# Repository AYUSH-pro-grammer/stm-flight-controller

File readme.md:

## Flight Controller
A flight controller I designed to understand more about how drones are stable and how all the sensors interact. I created my own custom PCB using KiCad which includes an STM32F405, IMU, Magnetometer and Barometer. It has been a great way to learn about embedded systems, sensor calibration and PCB design, but has shown me what can go wrong when creating hardware. There is still plenty to learn before its ready to fly!

## How it works

This is a flight controller board which I have designed to learn how drones work and how they stay stable. The board contains an STM32F405 microcontroller as well as several sensors.

STM32F405 - This is the central processing unit of the board. It collects and processes the data from the sensors.
MPU6050 - The MPU6050 contains an accelerometer and gyroscope to give an understanding of the movement, rotation and tilting of the drone.
LIS3MDL - The LIS3MDL contains a magnetometer, which works like a digital compass.
BMP280 - The BMP280 gives information about the air pressure and temperature. The pressure can be used to determine the altitude of the drone.
Power management - There is a power management circuit on the board to provide the correct voltages to each of the components.
Communication - The sensors are connected to the STM32F405 using I2C. This means the microcontroller can collect the data from the sensors.

## Assembly

Put the components together following the KiCad PCB and BOM layout. Pay attention to the orientation of the components (particularly the ICs, diodes and connectors). Once assembled, make sure there are no solder bridges or incorrect solder joints before powering on.

## Programming

The STM32F405 can be programmed using the SWD connector. Simply connect the SWDIO, SWCLK and GND pins. Also connect the 3.3V reference pin. Using STM32CubeProgrammer the firmware can be flashed.

## Firmware

The firmware consists of using the Betaflight open source flight controller firmware ([https://github.com/betaflight/betaflight](https://github.com/betaflight/betaflight)). The board uses an STM32F405 with MPU6050, LIS3MDL and BMP280.

The firmware will need to be configured for the custom board. This includes pin configuration, sensor connection and so on. You can find the source code and build instructions in the Betaflight repository.

## Images

**Schematic View**

**PCB View**

**Front View**

**Back View**

# BOM 

| Reference | Component | Quantity | Link | Cost |
|---|---|---:|---|---:|
| C1; C5 | YAGEO 10pF 0402 | 2 | [LCSC](https://www.lcsc.com/product-detail/C3860506.html) | $0.0426 |
| C2 | CCTC 10uF 0805 | 1 | [LCSC](https://www.lcsc.com/product-detail/C380331.html) | $0.0420 |
| C3; C7; C13; C23; C24; C28; C29 | FH 100nF 0603 | 7 | [LCSC](https://www.lcsc.com/product-detail/C30926.html) | $0.0371 |
| C4; C6; C9; C11; C12; C17; C18; C19; C20; C21; C22 | FH 100nF 0603 | 11 | [LCSC](https://www.lcsc.com/product-detail/C30926.html) | $0.0583 |
| C8; C10 | Samsung 2.2uF 0603 | 2 | [LCSC](https://www.lcsc.com/product-detail/C23630.html) | $0.0240 |
| C14 | CCTC 10nF 0402 | 1 | [LCSC](https://www.lcsc.com/product-detail/C688874.html) | $0.0057 |
| C15; C16 | SAMWHA 1uF 0603 | 2 | [LCSC](https://www.lcsc.com/product-detail/C513775.html) | $0.0268 |
| C25; C26 | YAGEO 22uF 1210 | 2 | [LCSC](https://www.lcsc.com/product-detail/C5341638.html) | $1.0416 |
| C27 | KEMET 220pF 0603 | 1 | [LCSC](https://www.lcsc.com/product-detail/C3843887.html) | $0.1150 |
| C30 | Samsung Electro-Mechanics CL10A105KB8NNNC 1uF 50V 0603 | 1 | [LCSC](https://www.lcsc.com/product-detail/C15849.html) | $0.0159 |
| C31 | YAGEO 4.7uF 0805 25V | 1 | [LCSC](https://www.lcsc.com/product-detail/C5185457.html) | $0.0717 |
| C32 | FH 4.7uF 0805 25V | 1 | [LCSC](https://www.lcsc.com/product-detail/C274413.html) | $0.0617 |
| C33 | CCTC 10nF 0603 | 1 | [LCSC](https://www.lcsc.com/product-detail/C282516.html) | $0.0055 |
| C34 | FH 2.2nF 0603 | 1 | [LCSC](https://www.lcsc.com/product-detail/C1604.html) | $0.0109 |
| C35 | YAGEO 22pF 0603 | 1 | [LCSC](https://www.lcsc.com/product-detail/C2240294.html) | $0.0295 |
| C36 | YAGEO 10nF 0603 | 1 | [LCSC](https://www.lcsc.com/product-detail/C100042.html) | $0.0151 |
| C37; C38 | CCTC 47uF 1210 | 2 | [LCSC](https://www.lcsc.com/product-detail/C53327077.html) | $0.4938 |
| C39 | KEMET 100nF 0805 | 1 | [LCSC](https://www.lcsc.com/product-detail/C141162.html) | $0.0207 |
| D1 | DIODES SD103ATW-7-F Schottky diode array | 1 | [LCSC](https://www.lcsc.com/product-detail/C3758863.html) | $0.2775 |
| D2 | Hubei KENTO Blue LED 0603 | 1 | [LCSC](https://www.lcsc.com/product-detail/C2288.html) | $0.0104 |
| D3; D6 | Yongyu Red LED 0603 | 2 | [LCSC](https://www.lcsc.com/product-detail/C434419.html) | $0.0262 |
| D4 | Comchip SS54-HF | 1 | [LCSC](https://www.lcsc.com/product-detail/C3757794.html) | $1.0512 |
| D5 | High Diode BAT54C | 1 | [LCSC](https://www.lcsc.com/product-detail/C466637.html) | $0.0127 |
| FB1 | Murata BLM18PG121SN1D Ferrite Bead | 1 | [LCSC](https://www.lcsc.com/product-detail/C14709.html) | $0.0153 |
| FB2; FB3 | TAI-TECH HCB1608KF-121T30 120R Ferrite Bead 0603 | 2 | [LCSC](https://www.lcsc.com/product-detail/C353920.html) | $0.0174 |
| J1 | HMTCONN Micro-USB B SMD right-angle | 1 | [LCSC](https://www.lcsc.com/product-detail/C53121380.html) | $0.0704 |
| J2; J4; J23; J17; J18; J19; J20; J21; J22; J24; J25; J26; J28 | BOOMELE 2.54mm 1x40P male header strip (cut to length) | 2 | [LCSC](https://www.lcsc.com/product-detail/C2337.html) | $0.3150 |
| J3 | Hirose DM3AT-SF-PEJM5 MicroSD Connector | 1 | [LCSC](https://www.lcsc.com/product-detail/C114218.html) | $1.4048 |
| J29 | ronghe RH-5016 SMD Test Point (4.0x4.0mm pad) | 1 | [LCSC](https://www.lcsc.com/product-detail/C5199799.html) | $0.0926 |
| L1 | KOHERelec MDA7030-4R7M 4.7uH | 1 | [LCSC](https://www.lcsc.com/product-detail/C2847483.html) | $0.6353 |
| R1 | YAGEO 1k 0603 | 1 | [LCSC](https://www.lcsc.com/product-detail/C22548.html) | $0.0053 |
| R2 | SEI 332k 1206 | 1 | [LCSC](https://www.lcsc.com/product-detail/C2486051.html) | $0.0145 |
| R3; R4; R12; R19 | YAGEO 1.5k 0603 | 4 | [LCSC](https://www.lcsc.com/product-detail/C114668.html) | $0.0132 |
| R5 | Vishay 10k 0805 | 1 | [LCSC](https://www.lcsc.com/product-detail/C844937.html) | $0.0093 |
| R6; R7; R8; R9; R10; R11 | YAGEO 4.7k 0603 | 6 | [LCSC](https://www.lcsc.com/product-detail/C99782.html) | $0.0192 |
| R15 | SEI 35.7k 1206 | 1 | [LCSC](https://www.lcsc.com/product-detail/C2533888.html) | $0.1044 |
| R16 | YAGEO 0 ohm 0603 | 1 | [LCSC](https://www.lcsc.com/product-detail/C95177.html) | $0.0021 |
| R17 | TE Connectivity 10.5k 1206 | 1 | [LCSC](https://www.lcsc.com/product-detail/C2084092.html) | $0.2813 |
| R18 | YAGEO RT0603BRD073K2L 3.2k 0603 | 1 | [LCSC](https://www.lcsc.com/product-detail/C861375.html) | $0.0371 |
| SW1 | C&K PCM12 SPDT Slide Switch | 1 | [LCSC](https://www.lcsc.com/product-detail/C221841.html) | $1.2754 |
| SW2 | C&K PTS647 Tactile Switch | 1 | [LCSC](https://www.lcsc.com/product-detail/C2800043.html) | $0.2704 |
| U1 | TDK InvenSense MPU-6050 | 1 | [LCSC](https://www.lcsc.com/product-detail/C24112.html) | $20.2250 |
| U2 | ST STM32F405RGT6 | 1 | [LCSC](https://www.lcsc.com/product-detail/C15742.html) | $6.9460 |
| U3 | AMS1117-3.3 | 1 | [LCSC](https://www.lcsc.com/product-detail/C6186.html) | $0.2093 |
| U4 | ST LIS3MDLTR | 1 | [LCSC](https://www.lcsc.com/product-detail/C478483.html) | $3.7855 |
| U5 | Bosch BMP280 Digital Pressure Sensor | 1 | [Robu](https://robu.in/product/bosch-bmp280-digital-pressure-sensor/) | $8.3900 |
| U6 | TI TPS5431DDA | 1 | [LCSC](https://www.lcsc.com/product-detail/C1355446.html) | $3.7620 |
| U7 | ST USBLC6-2SC6 | 1 | [LCSC](https://www.lcsc.com/product-detail/C7519.html) | $0.1786 |
| Y1 | DIODES FY1600066 16MHz Crystal | 1 | [LCSC](https://www.lcsc.com/product-detail/C5717615.html) | $1.0077 |
| PCB | PCB fabrication | 1 | — | $8.00 |
| **TOTAL** | **Components + PCB fabrication** | | | **$60.5830** |

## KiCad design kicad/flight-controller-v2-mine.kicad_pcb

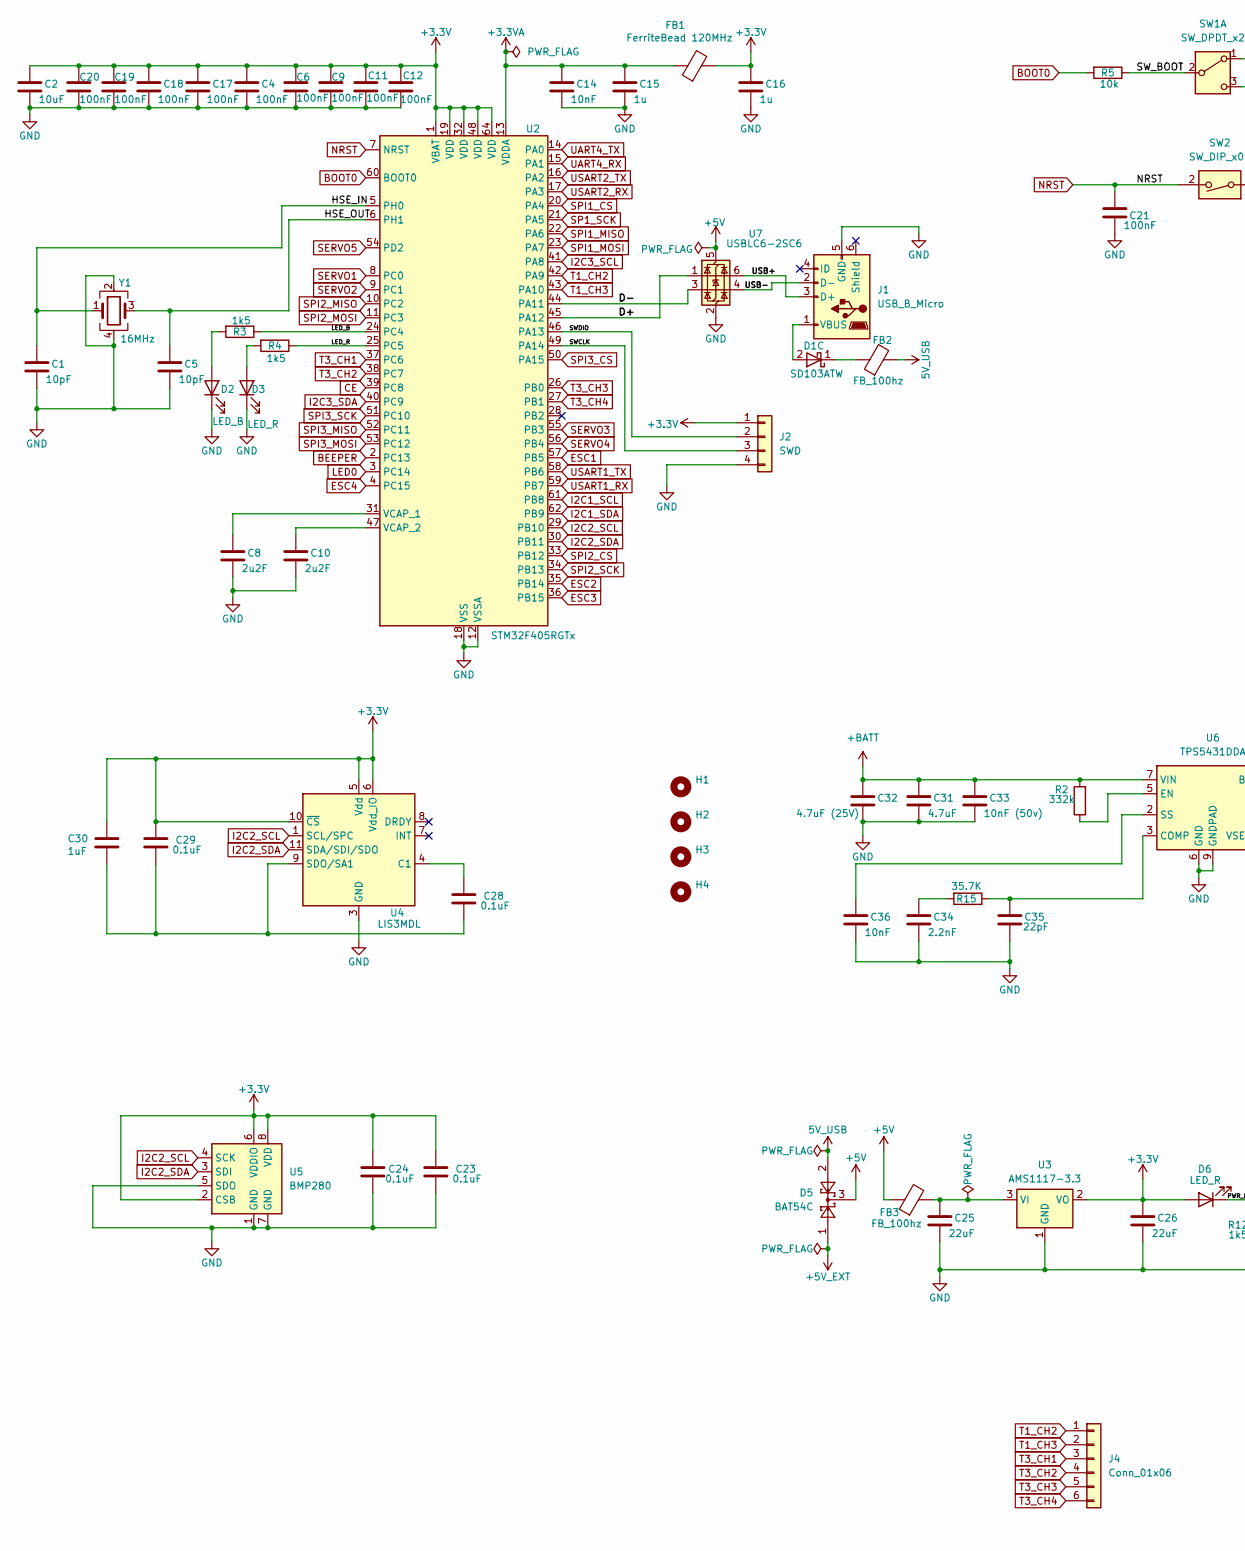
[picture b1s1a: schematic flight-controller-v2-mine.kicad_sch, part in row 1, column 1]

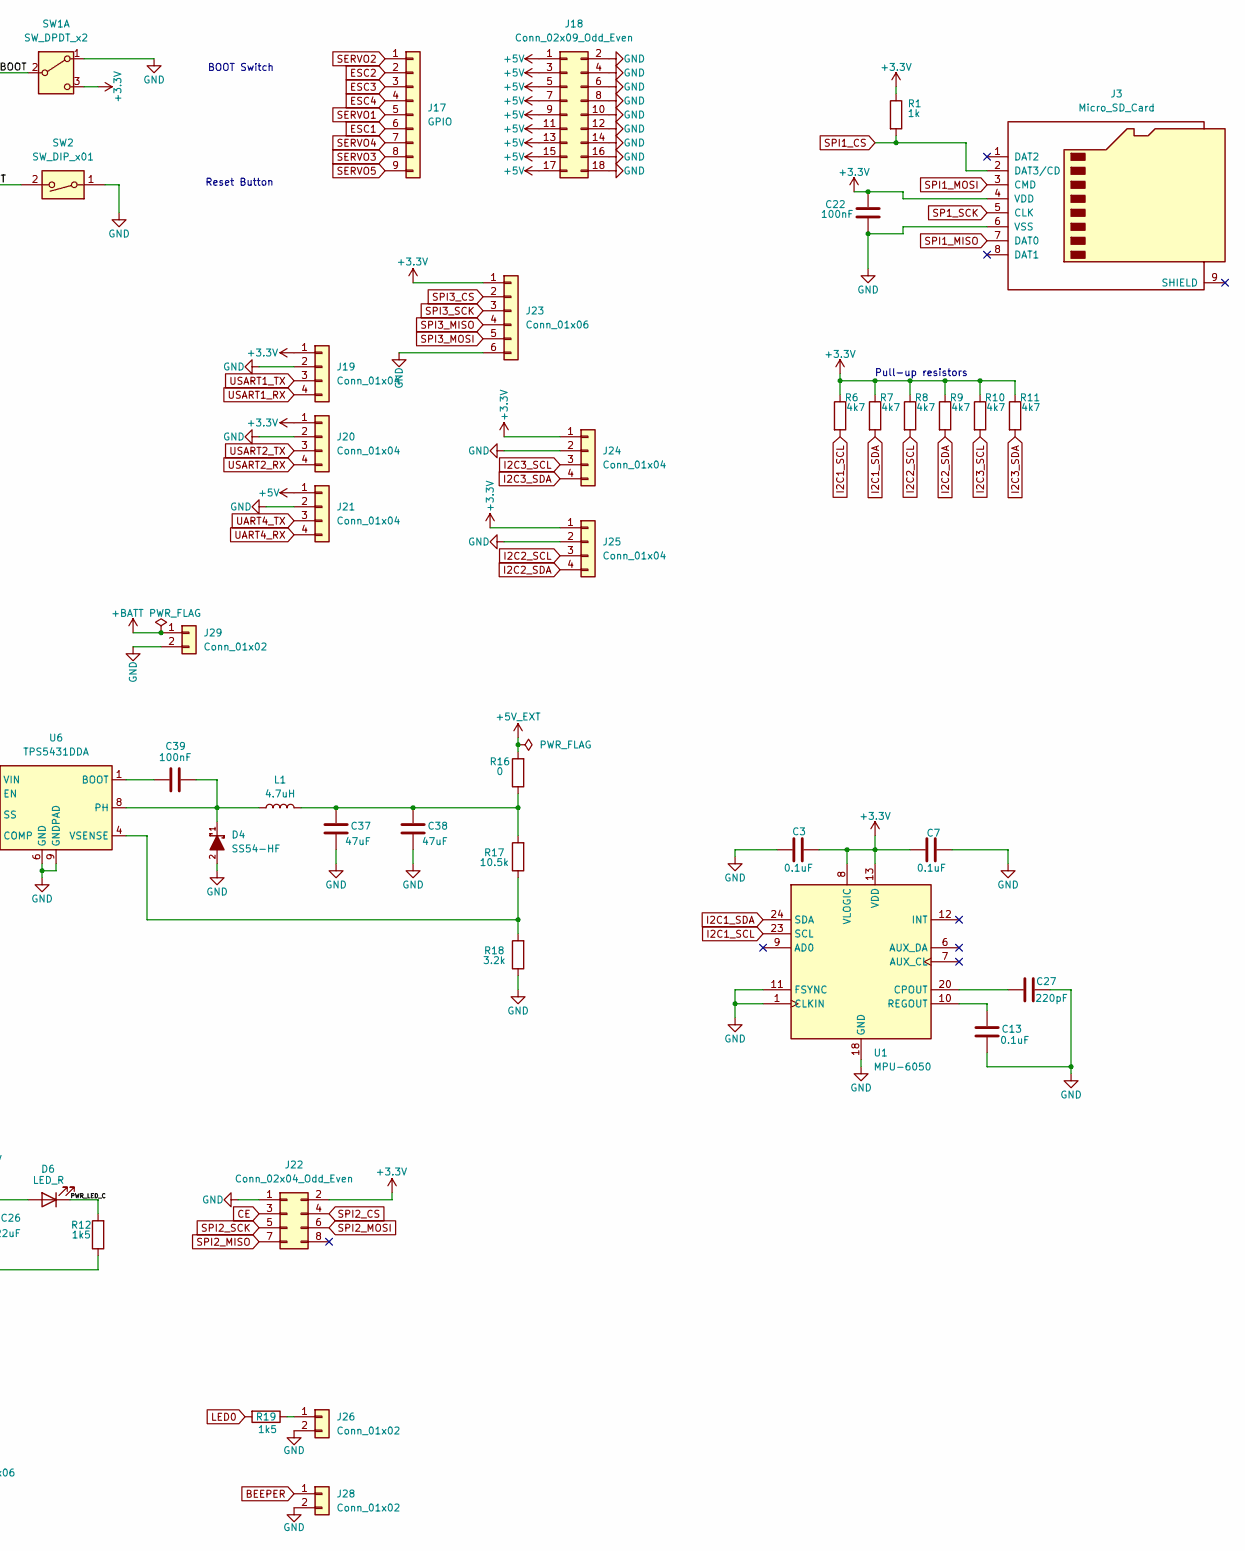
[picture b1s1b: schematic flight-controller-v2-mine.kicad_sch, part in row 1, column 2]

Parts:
C1, C5: 10pF; C_0402_1005Metric
C2: 10uF; C_0805_2012Metric
C3, C7, C13, C23, C24, C28, C29: 0.1uF; C_0603_1608Metric
C4, C6, C9, C11, C12, C17, C18, C19, C20, C21, C22: 100nF; C_0603_1608Metric
C8, C10: 2u2F; C_0603_1608Metric
C14: 10nF; C_0402_1005Metric
C15, C16: 1u; C_0603_1608Metric
C25, C26: 22uF; C_1210_3225Metric
C27: 220pF; C_0603_1608Metric
C30: 1uF; C_0603_1608Metric
C31: 4.7uF; C_0805_2012Metric
C32: 4.7uF (25V); C_0805_2012Metric
C33: 10nF (50v); C_0603_1608Metric
C34: 2.2nF; C_0603_1608Metric
C35: 22pF; C_0603_1608Metric
C36: 10nF; C_0603_1608Metric
C37, C38: 47uF; C_1210_3225Metric
C39: 100nF; C_0805_2012Metric
D1: SD103ATW; D_SOD-123
D2: LED_B; LED_0603_1608Metric
D3, D6: LED_R; LED_0603_1608Metric
D4: SS54-HF; D_SMA; MOUSER_PART_NUMBER 750-SS54-HF
D5: BAT54C; SOT-23
FB1: FerriteBead 120MHz; L_0603_1608Metric
FB2, FB3: FB_100hz; L_0603_1608Metric
H1, H2, H3, H4: MountingHole; MountingHole_4.3mm_M4_Pad_Via
J1: USB_B_Micro; USB_Mini-B_Lumberg_2486_01_Horizontal
J2: SWD; PinHeader_1x04_P2.54mm_Vertical
J3: Micro_SD_Card; microSD_HC_Hirose_DM3AT-SF-PEJM5
J4, J23: Conn_01x06; PinHeader_1x06_P2.54mm_Vertical
J17: GPIO; PinHeader_1x09_P2.54mm_Vertical
J18: Conn_02x09_Odd_Even; PinHeader_2x09_P2.54mm_Vertical
J19, J20, J21, J24, J25: Conn_01x04; PinHeader_1x04_P2.54mm_Vertical
J22: Conn_02x04_Odd_Even; PinHeader_2x04_P2.54mm_Vertical
J26, J28: Conn_01x02; PinHeader_1x02_P2.54mm_Vertical
J29: Conn_01x02; TestPoint_Pad_4.0x4.0mm
L1: 4.7uH; L_KOHERelec_MDA7030
R1: 1k; R_0603_1608Metric
R2: 332k; R_1206_3216Metric
R3, R4, R12, R19: 1k5; R_0603_1608Metric
R5: 10k; R_0805_2012Metric
R6, R7, R8, R9, R10, R11: 4k7; R_0603_1608Metric
R15: 35.7K; R_1206_3216Metric
R16: 0; R_0603_1608Metric
R17: 10.5k; R_1206_3216Metric
R18: 3.2k; R_0603_1608Metric
SW1: SW_DPDT_x2; SW_SPDT_PCM12
SW2: SW_DIP_x01; SW_SPST_PTS647_Sx38
U1: MPU-6050; InvenSense_QFN-24_4x4mm_P0.5mm
U2: STM32F405RGTx; LQFP-64_10x10mm_P0.5mm
U3: AMS1117-3.3; SOT-223-3_TabPin2
U4: LIS3MDL; LGA-12_2x2mm_P0.5mm
U5: BMP280; Bosch_LGA-8_2x2.5mm_P0.65mm_ClockwisePinNumbering
U6: TPS5431DDA; TI_SO-PowerPAD-8_ThermalVias
U7: USBLC6-2SC6; SOT-23-6
Y1: 16MHz; Crystal_SMD_5032-4Pin_5.0x3.2mm

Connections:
5V_USB: D5.2, FB2.2
+3.3V: C2.1, C3.2, C4.1, C6.1, C7.1, C9.1, C11.1, C12.1, C16.1, C17.1, C18.1, C19.1, C20.1, C22.1, C23.2, C24.2, C26.1, C29.2, C30.2, D6.2 (A), FB1.2, J2.1, J3.4 (VDD), J19.1, J20.1, J22.2, J23.1, J24.1, J25.1, R1.1, R6.1, R7.1, R8.1, R9.1, R10.1, R11.1, SW1.3 (C), U1.8 (VLOGIC), U1.13 (VDD), U2.1 (VBAT), U2.19 (VDD), U2.32 (VDD), U2.48 (VDD), U2.64 (VDD), U3.2 (VO), U4.5 (Vdd), U4.6 (Vdd_IO), U4.10 (~CS), U5.2 (CSB), U5.6 (VDDIO), U5.8 (VDD)
+3.3VA: C14.1, C15.1, FB1.1, U2.13 (VDDA)
+5V: D5.3, FB3.1, J18.1, J18.3, J18.5, J18.7, J18.9, J18.11, J18.13, J18.15, J18.17, J21.1, U7.5 (VBUS)
+5V_EXT: D5.1, R16.2
+BATT: C31.1, C32.1, C33.1, J29.1, R2.2, U6.7 (VIN)
/D+: U2.45 (PA12), U7.1 (I/O1)
/D-: U2.44 (PA11), U7.3 (I/O2)
/HSE_IN: C1.1, U2.5 (PH0), Y1.1
/HSE_OUT: C5.1, U2.6 (PH1), Y1.3
/LED_B: R3.1, U2.24 (PC4)
/LED_R: R4.1, U2.25 (PC5)
/SWCLK: J2.3, U2.49 (PA14)
/SWDIO: J2.2, U2.46 (PA13)
/SW_BOOT: R5.1, SW1.2 (B)
/USB+: J1.3 (D+), U7.6 (I/O1)
/USB-: J1.2 (D-), U7.4 (I/O2)
/power and connectors/PWR_LED_C: D6.1 (K), R12.2
BEEPER: J28.1, U2.2 (PC13)
BOOT0: R5.2, U2.60 (BOOT0)
CE: J22.3, U2.39 (PC8)
ESC1: J17.6, U2.57 (PB5)
ESC2: J17.2, U2.35 (PB14)
ESC3: J17.3, U2.36 (PB15)
ESC4: J17.4, U2.4 (PC15)
GND: C1.2, C2.2, C3.1, C4.2, C5.2, C6.2, C7.2, C8.2, C9.2, C10.2, C11.2, C12.2, C13.2, C14.2, C15.2, C16.2, C17.2, C18.2, C19.2, C20.2, C21.2, C22.2, C23.1, C24.1, C25.2, C26.2, C27.2, C31.2, C32.2, C33.2, C34.2, C35.2, C36.2, C37.2, C38.2, D2.1 (K), D3.1 (K), D4.2, J1.5 (GND), J2.4, J3.6 (VSS), J18.2, J18.4, J18.6, J18.8, J18.10, J18.12, J18.14, J18.16, J18.18, J19.2, J20.2, J21.2, J22.1, J23.6, J24.2, J25.2, J26.2, J28.2, J29.2, R12.1, R18.1, SW1.1 (A), SW2.1, U1.1 (CLKIN), U1.11 (FSYNC), U1.18 (GND), U2.12 (VSSA), U2.18 (VSS), U3.1 (GND), U4.3 (GND), U5.1 (GND), U5.5 (SDO), U5.7 (GND), U6.6 (GND), U6.9 (GNDPAD), U7.2 (GND), Y1.2, Y1.4
I2C1_SCL: R6.2, U1.23 (SCL), U2.61 (PB8)
I2C1_SDA: R7.2, U1.24 (SDA), U2.62 (PB9)
I2C2_SCL: J25.3, R8.2, U2.29 (PB10), U4.1 (SCL/SPC), U5.4 (SCK)
I2C2_SDA: J25.4, R9.2, U2.30 (PB11), U4.11 (SDA/SDI/SDO), U5.3 (SDI)
I2C3_SCL: J24.3, R10.2, U2.41 (PA8)
I2C3_SDA: J24.4, R11.2, U2.40 (PC9)
LED0: R19.2, U2.3 (PC14)
NRST: C21.1, SW2.2, U2.7 (NRST)
unnamed: C34.1, R15.2
unnamed: C37.1, C38.1, L1.2, R16.1, R17.2
unnamed: D1.2 (A), J1.1 (VBUS)
unnamed: D1.1 (K), FB2.1
unnamed: D2.2 (A), R3.2
unnamed: D3.2 (A), R4.2
unnamed: J26.1, R19.1
unnamed: C27.1, U1.20 (CPOUT)
unnamed: C13.1, U1.10 (REGOUT)
unnamed: C8.1, U2.31 (VCAP_1)
unnamed: C10.1, U2.47 (VCAP_2)
unnamed: C25.1, FB3.2, U3.3 (VI)
unnamed: C28.2, U4.4 (C1)
unnamed: C28.1, C29.1, C30.1, U4.9 (SDO/SA1)
unnamed: C39.1, U6.1 (BOOT)
unnamed: C35.1, R15.1, U6.3 (COMP)
unnamed: R2.1, U6.5 (EN)
unnamed: C39.2, D4.1, L1.1, U6.8 (PH)
unnamed: C36.1, U6.2 (SS)
unnamed: R17.1, R18.2, U6.4 (VSENSE)
SERVO1: J17.5, U2.8 (PC0)
SERVO2: J17.1, U2.9 (PC1)
SERVO3: J17.8, U2.55 (PB3)
SERVO4: J17.7, U2.56 (PB4)
SERVO5: J17.9, U2.54 (PD2)
SP1_SCK: J3.5 (CLK), U2.21 (PA5)
SPI1_CS: J3.2 (DAT3/CD), R1.2, U2.20 (PA4)
SPI1_MISO: J3.7 (DAT0), U2.22 (PA6)
SPI1_MOSI: J3.3 (CMD), U2.23 (PA7)
SPI2_CS: J22.4, U2.33 (PB12)
SPI2_MISO: J22.7, U2.10 (PC2)
SPI2_MOSI: J22.6, U2.11 (PC3)
SPI2_SCK: J22.5, U2.34 (PB13)
SPI3_CS: J23.2, U2.50 (PA15)
SPI3_MISO: J23.4, U2.52 (PC11)
SPI3_MOSI: J23.5, U2.53 (PC12)
SPI3_SCK: J23.3, U2.51 (PC10)
T1_CH2: J4.1, U2.42 (PA9)
T1_CH3: J4.2, U2.43 (PA10)
T3_CH1: J4.3, U2.37 (PC6)
T3_CH2: J4.4, U2.38 (PC7)
T3_CH3: J4.5, U2.26 (PB0)
T3_CH4: J4.6, U2.27 (PB1)
UART4_RX: J21.4, U2.15 (PA1)
UART4_TX: J21.3, U2.14 (PA0)
USART1_RX: J19.4, U2.59 (PB7)
USART1_TX: J19.3, U2.58 (PB6)
USART2_RX: J20.4, U2.17 (PA3)
USART2_TX: J20.3, U2.16 (PA2)

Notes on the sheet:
Reset Button
Pull-up resistors
BOOT Switch

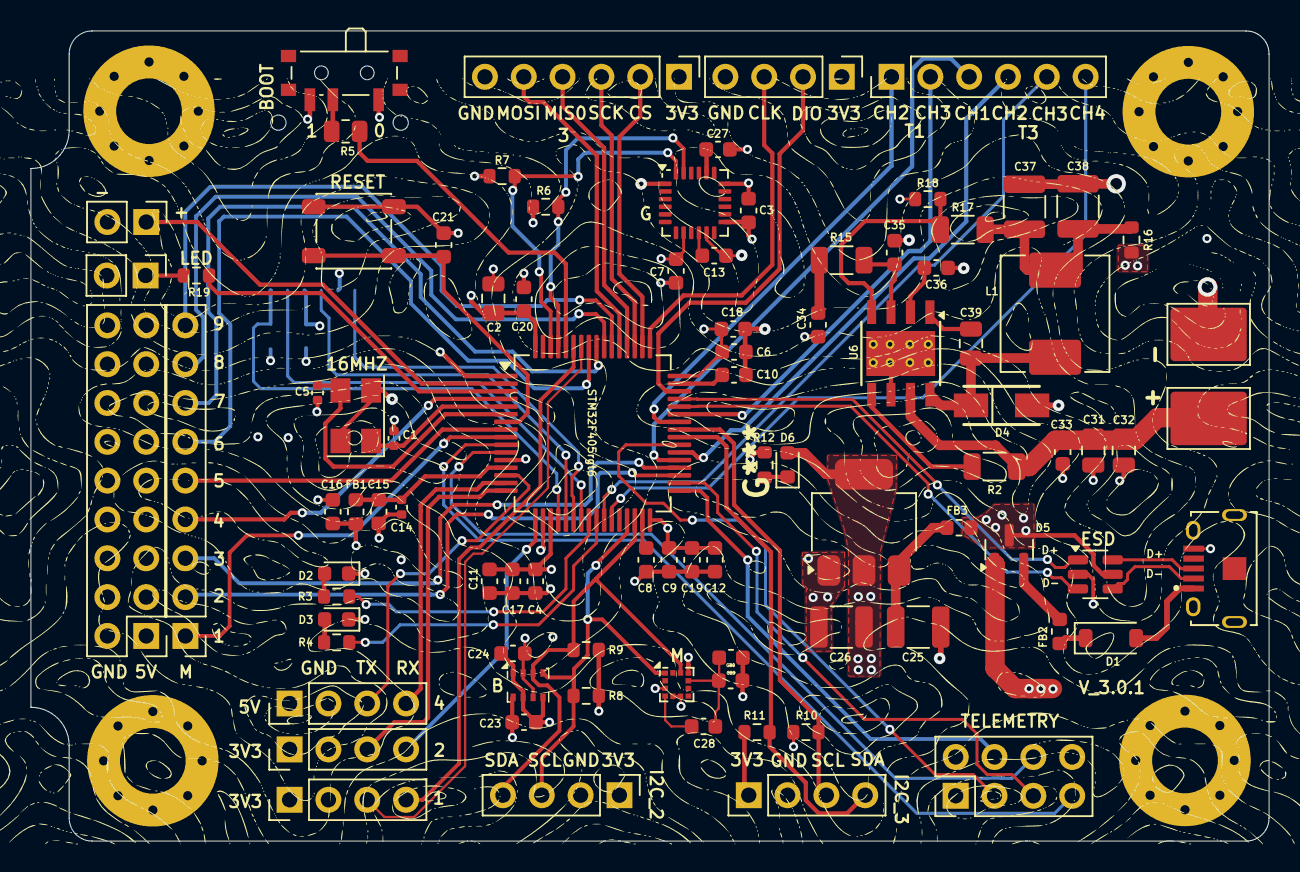
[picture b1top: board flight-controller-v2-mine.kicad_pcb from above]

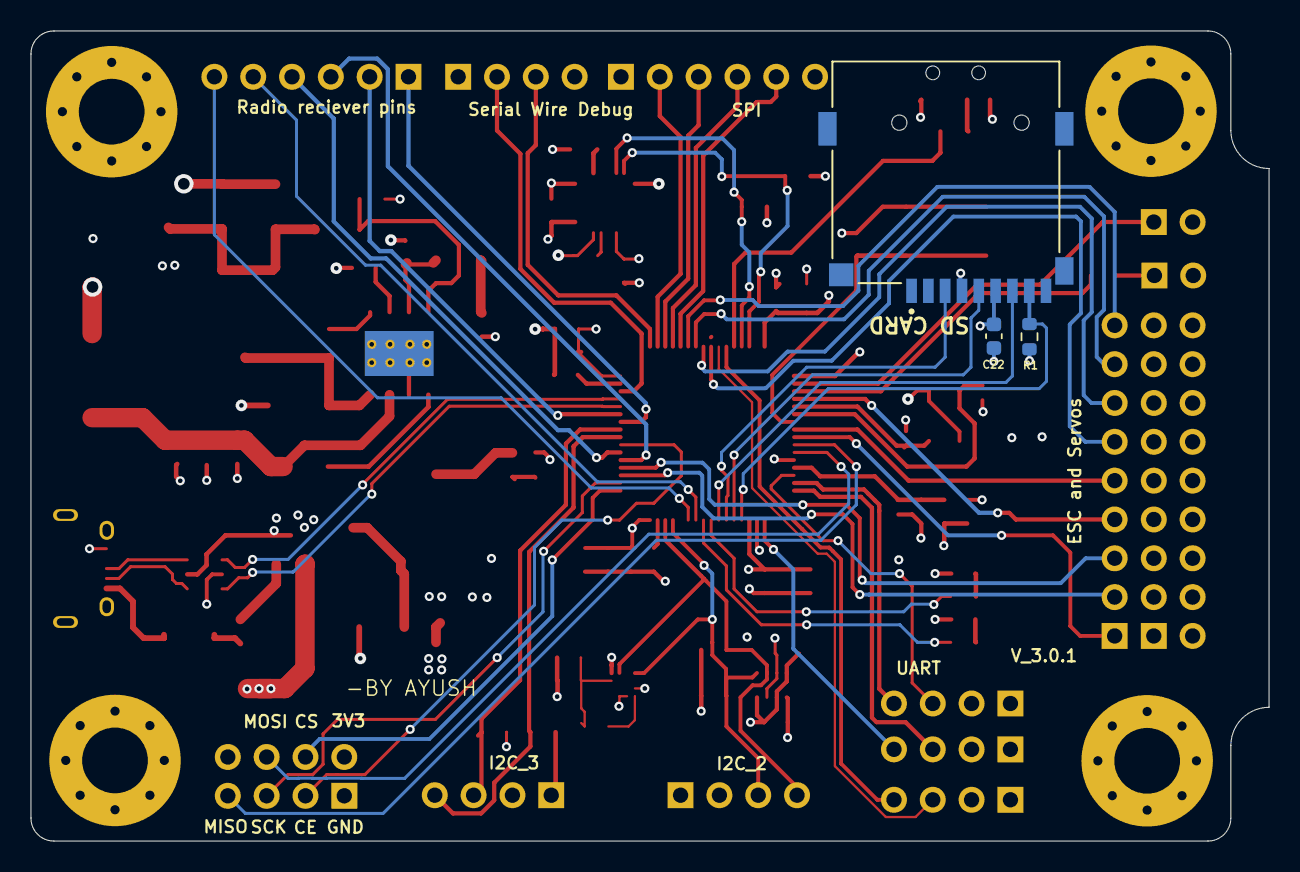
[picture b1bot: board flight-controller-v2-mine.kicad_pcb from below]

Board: 4 copper layers, 81.0 x 53.0 mm, 96 parts (3 on the bottom side), 83 nets.

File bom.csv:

Reference,Component,Quantity,Unit Price (USD),Product Link
"C1; C5","YAGEO 10pF 0402",2,0.0213,https://www.lcsc.com/product-detail/C3860506.html
"C2","CCTC 10uF 0805",1,0.0420,https://www.lcsc.com/product-detail/C380331.html
"C3; C7; C13; C23; C24; C28; C29","FH 100nF 0603",7,0.0053,https://www.lcsc.com/product-detail/C30926.html
"C4; C6; C9; C11; C12; C17; C18; C19; C20; C21; C22","FH 100nF 0603",11,0.0053,https://www.lcsc.com/product-detail/C30926.html
"C8; C10","Samsung 2.2uF 0603",2,0.0120,https://www.lcsc.com/product-detail/C23630.html
"C14","CCTC 10nF 0402",1,0.0057,https://www.lcsc.com/product-detail/C688874.html
"C15; C16","SAMWHA 1uF 0603",2,0.0134,https://www.lcsc.com/product-detail/C513775.html
"C25; C26","YAGEO 22uF 1210",2,0.5208,https://www.lcsc.com/product-detail/C5341638.html
"C27","KEMET 220pF 0603",1,0.1150,https://www.lcsc.com/product-detail/C3843887.html
"C30","Samsung Electro-Mechanics CL10A105KB8NNNC 1uF 50V 0603",1,N/A,https://www.lcsc.com/product-detail/C15849.html
"C31","YAGEO 4.7uF 0805 25V",1,0.0717,https://www.lcsc.com/product-detail/C5185457.html
"C32","FH 4.7uF 0805 25V",1,0.0617,https://www.lcsc.com/product-detail/C274413.html
"C33","CCTC 10nF 0603",1,0.0055,https://www.lcsc.com/product-detail/C282516.html
"C34","FH 2.2nF 0603",1,0.0109,https://www.lcsc.com/product-detail/C1604.html
"C35","YAGEO 22pF 0603",1,0.0295,https://www.lcsc.com/product-detail/C2240294.html
"C36","YAGEO 10nF 0603",1,0.0151,https://www.lcsc.com/product-detail/C100042.html
"C37; C38","CCTC 47uF 1210",2,0.2469,https://www.lcsc.com/product-detail/C53327077.html
"C39","KEMET 100nF 0805",1,0.0207,https://www.lcsc.com/product-detail/C141162.html
"D1","DIODES SD103ATW-7-F Schottky diode array - footprint check required",1,0.2775,https://www.lcsc.com/product-detail/C3758863.html
"D2","Hubei KENTO Blue LED 0603",1,0.0104,https://www.lcsc.com/product-detail/C2288.html
"D3; D6","Yongyu Red LED 0603",2,0.0131,https://www.lcsc.com/product-detail/C434419.html
"D4","Comchip SS54-HF",1,1.0512,https://www.lcsc.com/product-detail/C3757794.html
"D5","High Diode BAT54C",1,0.0127,https://www.lcsc.com/product-detail/C466637.html
"FB1","Murata BLM18PG121SN1D Ferrite Bead",1,0.0153,https://www.lcsc.com/product-detail/C14709.html
"FB2; FB3","TAI-TECH HCB1608KF-121T30 120R Ferrite Bead 0603",2,0.0087,https://www.lcsc.com/product-detail/C353920.html
"J1","HMTCONN Micro-USB B SMD right-angle - footprint check required",1,0.0704,https://www.lcsc.com/product-detail/C53121380.html
"J2; J4; J23; J17; J19; J20; J21; J24; J25; J26; J28","BOOMELE 2.54mm 1x40P male header strip - cut to length",2,0.1575,https://www.lcsc.com/product-detail/C2337.html
"J3","Hirose DM3AT-SF-PEJM5 MicroSD Connector",1,1.4048,https://www.lcsc.com/product-detail/C114218.html
"L1","KOHERelec MDA7030-4R7M 4.7uH",1,0.6353,https://www.lcsc.com/product-detail/C2847483.html
"R1","YAGEO 1k 0603",1,0.0053,https://www.lcsc.com/product-detail/C22548.html
"R2","SEI 332k 1206",1,0.0145,https://www.lcsc.com/product-detail/C2486051.html
"R3; R4; R12; R19","YAGEO 1.5k 0603",4,0.0033,https://www.lcsc.com/product-detail/C114668.html
"R5","Vishay 10k 0805",1,0.0093,https://www.lcsc.com/product-detail/C844937.html
"R6; R7; R8; R9; R10; R11","YAGEO 4.7k 0603",6,0.0032,https://www.lcsc.com/product-detail/C99782.html
"R15","SEI 35.7k 1206",1,0.1044,https://www.lcsc.com/product-detail/C2533888.html
"R16","YAGEO 0 ohm 0603",1,0.0021,https://www.lcsc.com/product-detail/C95177.html
"R17","TE Connectivity 10.5k 1206",1,0.2813,https://www.lcsc.com/product-detail/C2084092.html
"SW1","C&K PCM12 SPDT Slide Switch",1,1.2754,https://www.lcsc.com/product-detail/C221841.html
"SW2","C&K PTS647 Tactile Switch",1,0.2704,https://www.lcsc.com/product-detail/C2800043.html
"U1","TDK InvenSense MPU-6050",1,20.2250,https://www.lcsc.com/product-detail/C24112.html
"U2","ST STM32F405RGT6",1,6.9460,https://www.lcsc.com/product-detail/C15742.html
"U3","AMS1117-3.3",1,0.2093,https://www.lcsc.com/product-detail/C6186.html
"U4","ST LIS3MDLTR",1,3.7855,https://www.lcsc.com/product-detail/C478483.html
"U5","Bosch BMP280 Digital Pressure Sensor",1,N/A,https://robu.in/product/bosch-bmp280-digital-pressure-sensor/
"U6","TI TPS5431DDA",1,3.7620,https://www.lcsc.com/product-detail/C1355446.html
"U7","ST USBLC6-2SC6",1,0.1786,https://www.lcsc.com/product-detail/C7519.html
"Y1","DIODES FY1600066 16MHz Crystal",1,1.0077,https://www.lcsc.com/product-detail/C5717615.html
"", "PCB", 1, 8, "https://jlcpcb.com"
"TOTAL","Known-price items subtotal",,52,
